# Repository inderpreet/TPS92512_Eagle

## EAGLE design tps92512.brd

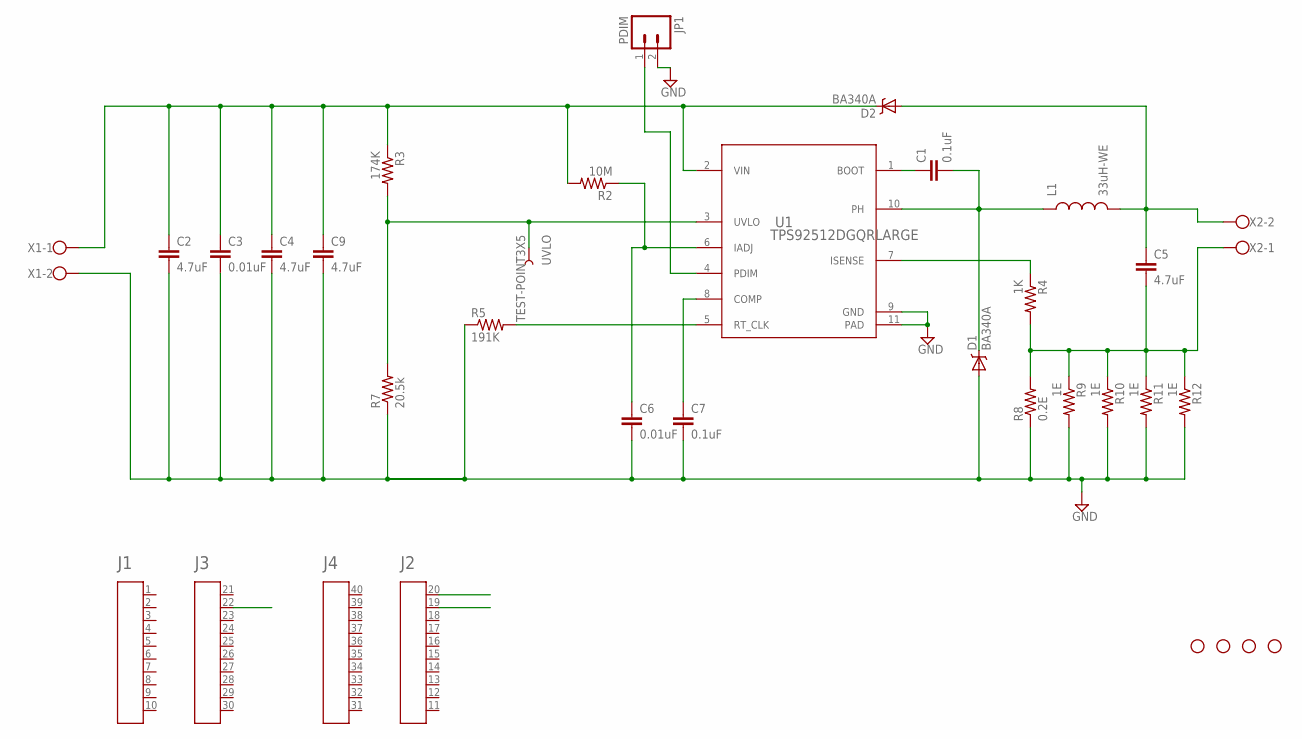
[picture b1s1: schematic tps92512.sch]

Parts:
A1: HEADER4X10-BOOSTERPACK; 4X10-BOOSTERPACK
C1, C7: 0.1uF; 0805
C2, C4, C9: 4.7uF; 1210
C3, C6: 0.01uF; 0805
C5: 4.7uF; 1206
D1, D2: BA340A; SMA-DIODE
JP1: PDIM; 1X02_LOCK
L1: 33uH-WE; DR1030
R2: 10M; R0805
R3: 174K; R0805
R4: 1K; R0805
R5: 191K; R0805
R7: 20.5k; R0805
R8: 0.2E; R1210W
R9, R10, R11, R12: 1E; R0805
STANDOFF1, STANDOFF2, STANDOFF3, STANDOFF4: STAND-OFF
U1: TPS92512DGQRLARGE; DGQ0010D_M
UVLO: TEST-POINT3X5; PAD.03X.05
X1, X2: W237-102

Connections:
GND: A1.20, A1.22, C2.2, C3.2, C4.2, C6.2, C7.2, C9.2, D1.A, JP1.2, R5.1, R7.1, R8.1, R9.2, R10.2, R11.2, R12.2, U1.9 (GND), U1.11 (PAD), X1.2
LEDMINUS: C5.2, R4.2, R8.2, R9.1, R10.1, R11.1, R12.1, X2.1
LEDPLUS: C5.1, D2.A, L1.2, X2.2
unnamed: C7.1, U1.8 (COMP)
unnamed: C6.1, R2.1, U1.6 (IADJ)
unnamed: C1.1, U1.1 (BOOT)
unnamed: R5.2, U1.5 (RT_CLK)
unnamed: R3.2, R7.2, U1.3 (UVLO), UVLO.P$1
unnamed: R4.1, U1.7 (ISENSE)
PDIM: A1.19, JP1.1, U1.4 (PDIM)
PINTEN: C1.2, D1.C, L1.1, U1.10 (PH)
VIN: C2.1, C3.1, C4.1, C9.1, D2.C, R2.2, R3.1, U1.2 (VIN), X1.1

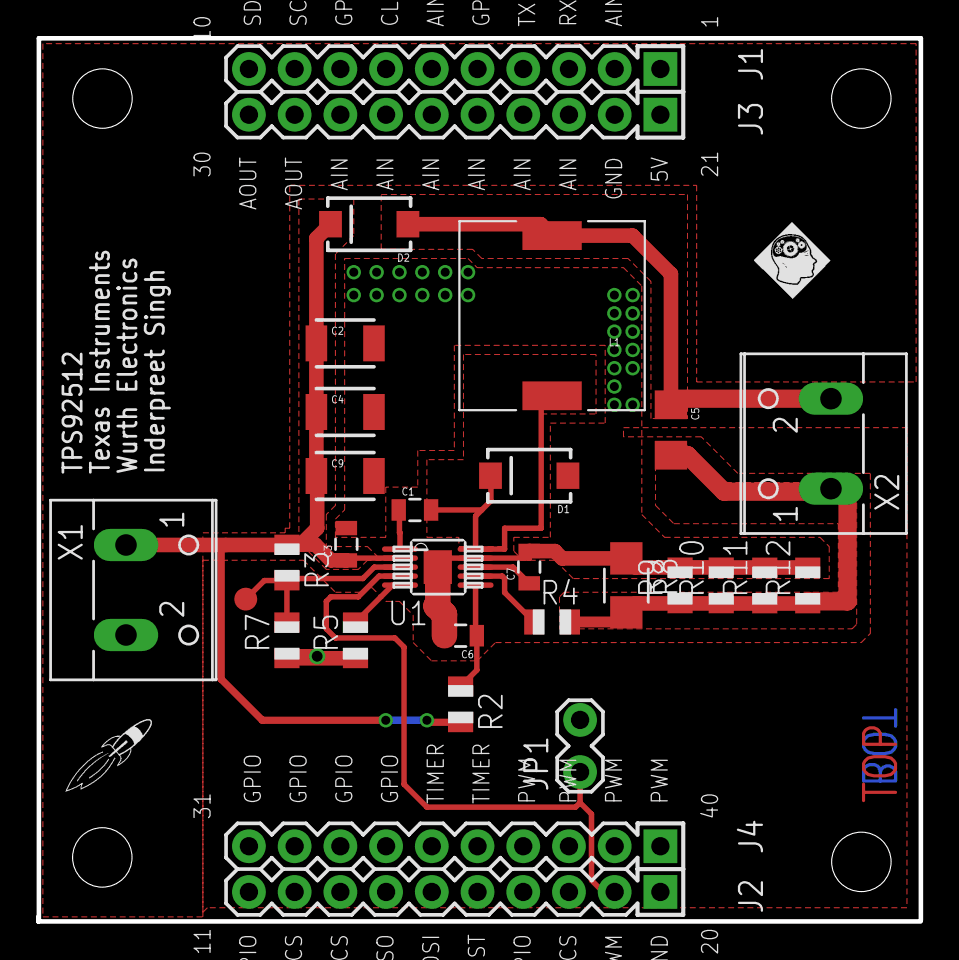
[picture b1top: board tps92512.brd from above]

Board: 2 copper layers, 49.0 x 49.1 mm, 32 parts (0 on the bottom side), 12 nets.

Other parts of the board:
U$3: LOGO-ROCKET

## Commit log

2017-07-27 To OshPark

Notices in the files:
parts and their libraries:
SparkFun-Capacitors: Licensing: CC v3.0 Share-Alike You are welcome to use this library for commercial purposes.
